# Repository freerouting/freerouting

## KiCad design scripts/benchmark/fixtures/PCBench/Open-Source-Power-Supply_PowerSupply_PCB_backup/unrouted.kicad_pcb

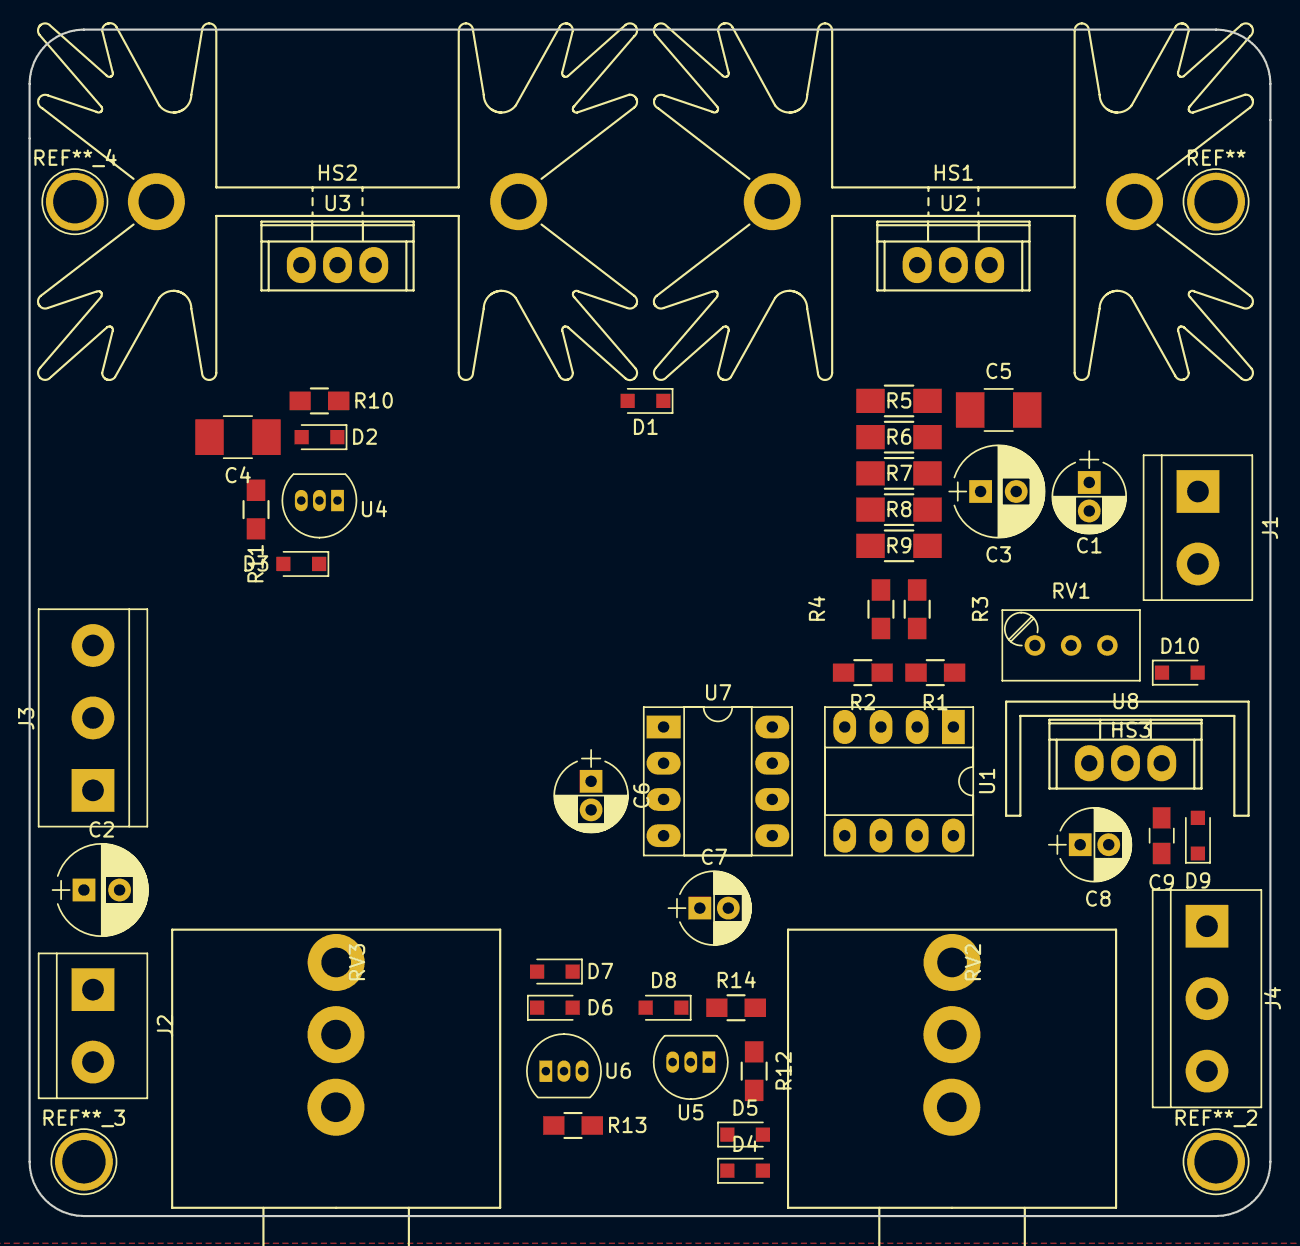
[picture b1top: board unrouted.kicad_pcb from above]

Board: 2 copper layers, 87.0 x 83.2 mm, 51 parts (0 on the bottom side), 23 nets, no tracks yet.

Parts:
C1, C6, C7, C8: 10u; CP_Radial_D5.0mm_P2.00mm
C2: 47uF electro; CP_Radial_D6.3mm_P2.50mm
C3: 47u; CP_Radial_D6.3mm_P2.50mm
C4: 4.7u; C_1210_HandSoldering
C5: 4.7u (optional); C_1210_HandSoldering
C9: 0.1u; C_0805_HandSoldering
D1, D2, D3, D9, D10: 1N5819; D_SOD-323_HandSoldering
D4, D5, D6, D7, D8: 1N4448; D_SOD-323_HandSoldering
HS1, HS2: Heatsink; Heatsink_Fischer_SK129-STS_42x25mm_2xDrill2.5mm
HS3: Heatsink; TO220-Small-16mmx8mm
J1: Input Voltage; bornier2
J2: Output Voltage; bornier2
J3: Voltage Meter; bornier3
J4: Current Meter; bornier3
R1, R2: 50k; R_0805_HandSoldering
R3, R4: 10k; R_0805_HandSoldering
R5, R6, R7, R8, R9: 10; R_1206_HandSoldering
R10: 1k; R_0805_HandSoldering
R11, R13: 15; R_0805_HandSoldering
R12: 33; R_0805_HandSoldering
R14: 330; R_0805_HandSoldering
RV1: 100 (multiturn); Potentiometer_Trimmer_Bourns_3296W
RV2, RV3: 10k; Potentiometer-3596S-10k-Pot
U1: LT1013; DIP-8_W7.62mm_Socket_LongPads
U2: LT1086; TO-220
U3: LM1117-ADJ; TO-220
U4, U5, U6: LM334Z; TO-92_Inline_Narrow_Oval
U7: ICL7660; DIP-8_W7.62mm_Socket_LongPads
U8: LM7812CT; TO-220

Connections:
+12V: C9.1, D9.2, D10.1, J3.1, J4.1, U7.8, U8.3
+16V: C1.1, C8.1, D1.1, D9.1, J1.1, U1.8, U2.3, U8.1
-12V: C7.2, D8.1, R11.2, R13.2, R14.2, U1.4, U4.3, U6.3, U7.5
CurrentMeter: J4.2, R1.1, U1.1
GND: C1.2, C2.2, C3.2, C4.2, C5.2, C7.1, C8.2, C9.2, D3.2, D7.2, D10.2, J1.2, J2.2, J3.3, J4.3, R2.2, U7.3, U8.2
unnamed: C3.1, R4.2, R5.1, R6.1, R7.1, R8.1, R9.1, RV1.1, U3.3
unnamed: C4.1, D2.2, R10.2, RV3.1, U3.1
unnamed: C5.1, RV2.2, U2.1
unnamed: C6.1, U7.2
unnamed: C6.2, U7.4
unnamed: D4.1, D5.2
unnamed: D4.2, RV1.2, RV1.3, RV2.3
unnamed: D5.1, RV2.1, U5.1
unnamed: D6.1, RV3.2, RV3.3, U6.1
unnamed: D6.2, D7.1
unnamed: D8.2, R12.2, U5.3
unnamed: R1.2, R4.1, U1.2
unnamed: R2.1, R3.1, U1.3
unnamed: R3.2, R5.2, R6.2, R7.2, R8.2, R9.2, U2.2
unnamed: R11.1, U4.2
unnamed: R12.1, R14.1, U5.2
unnamed: R13.1, U6.2
VoltageMeter: C2.1, D1.2, D2.1, D3.1, J2.1, J3.2, R10.1, U3.2, U4.1

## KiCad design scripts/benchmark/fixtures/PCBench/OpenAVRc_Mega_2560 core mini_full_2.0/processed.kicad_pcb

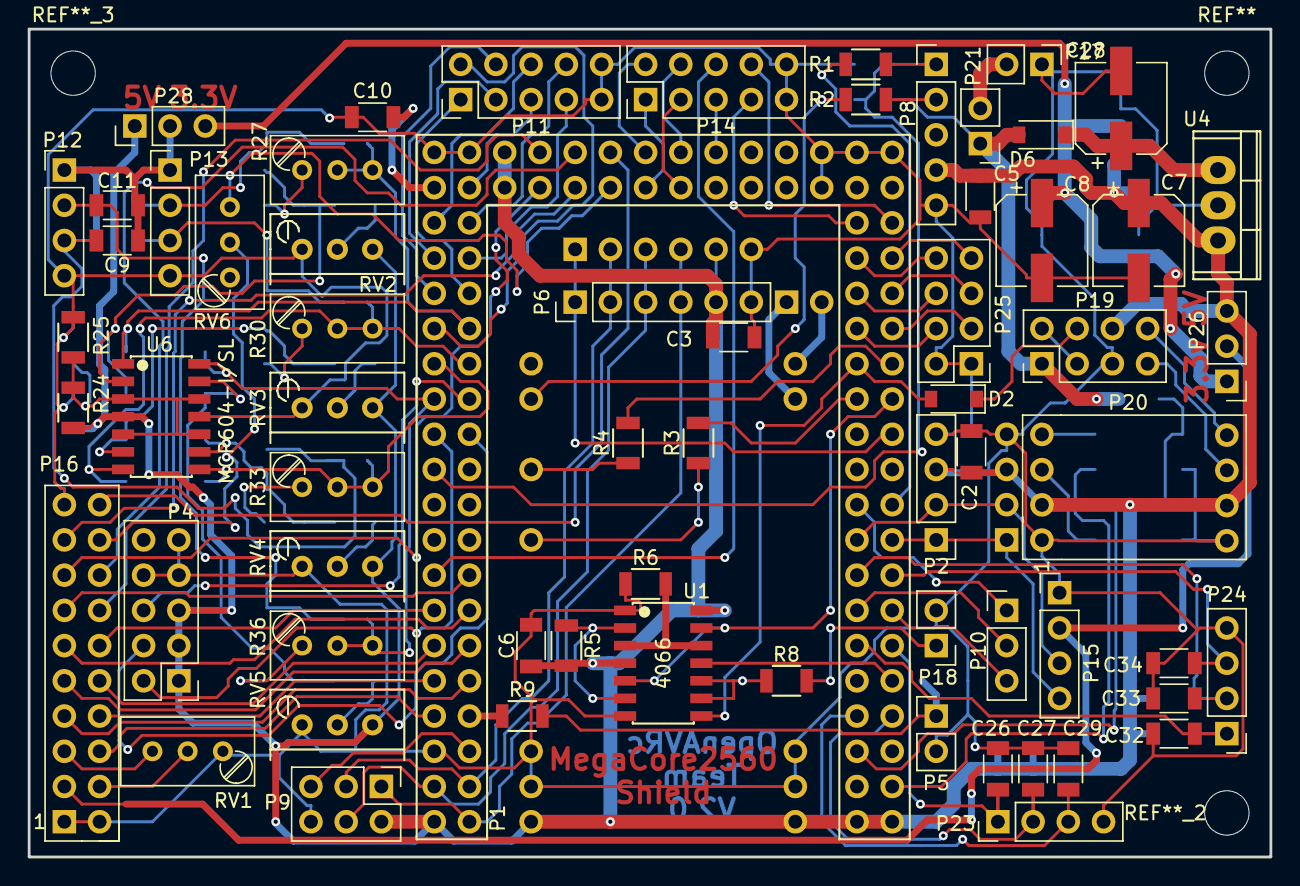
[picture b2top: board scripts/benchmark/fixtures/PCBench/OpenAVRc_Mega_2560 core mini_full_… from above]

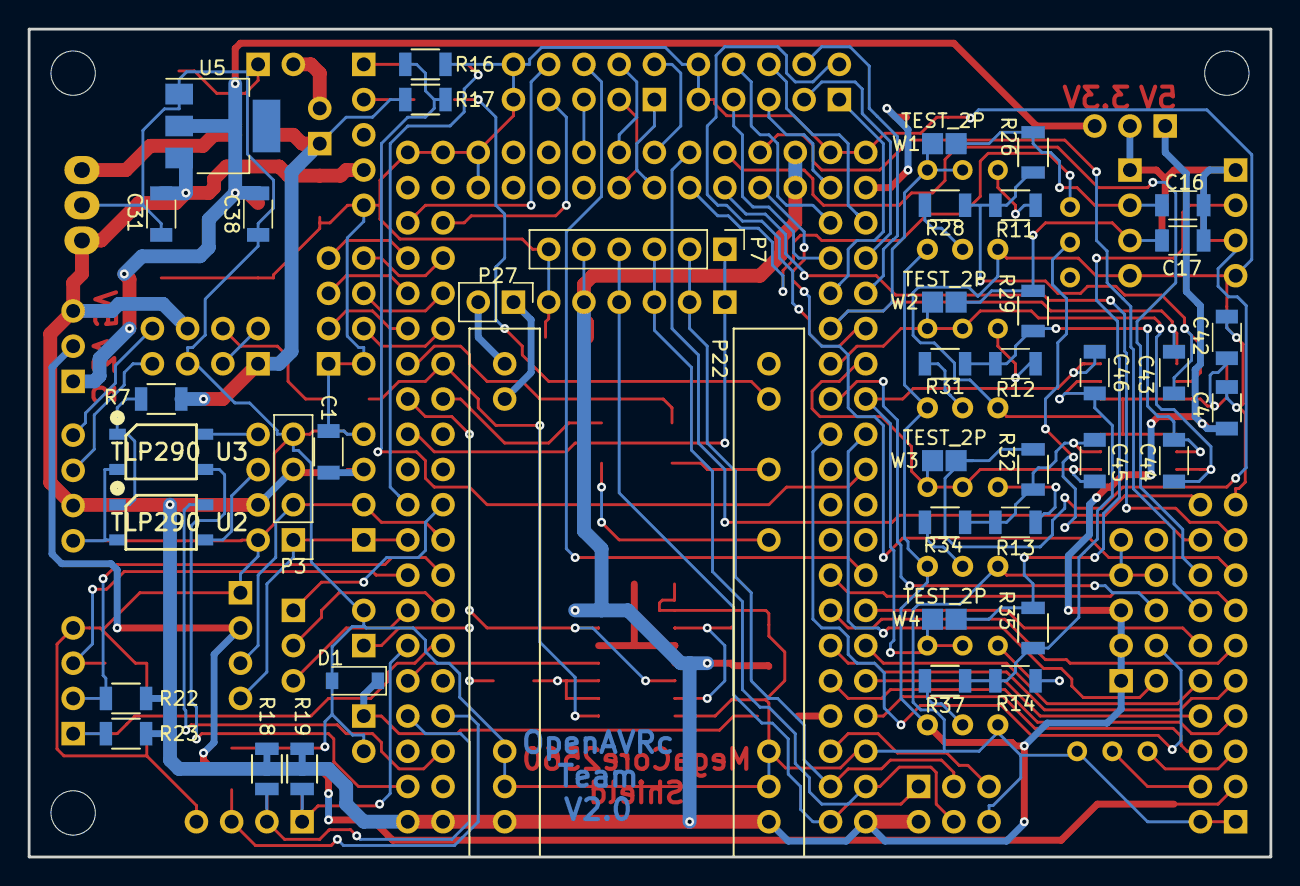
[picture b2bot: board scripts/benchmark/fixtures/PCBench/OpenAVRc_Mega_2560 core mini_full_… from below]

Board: 2 copper layers, 89.5 x 59.7 mm, 107 parts (42 on the bottom side), 117 nets.

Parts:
C1, C2, C3, C5: 47nF; C_1206
C4, C6, C9, C10, C11, C16, C17, C26, C27, C29, C31, C32, C33, C34, C38: 100nF; C_1206
C7, C8, C28: 47µF; CP_Elec_6.3x5.3
C42: 6.8nF; C_1206
C43, C44, C45, C46: 22nF; C_1206
D1, D2, D6: MBR0520; D_SOD-123
P1: 2560-core; Connectors-2560-core
P2: Clock; Pin_Header_Straight_1x04_Pitch2.54mm
P3: Option; Pin_Header_Straight_1x04_Pitch2.54mm
P4: Potentiometre; Pin_Header_Straight_2x05_Pitch2.54mm
P5: Vibreur; Pin_Header_Straight_1x02_Pitch2.54mm
P6: Micro_sd; Pin_Header_Straight_1x06_Pitch2.54mm
P7: Option; Pin_Header_Straight_1x06_Pitch2.54mm
P8: Audio; Pin_Header_Straight_1x05_Pitch2.54mm
P9: SPI; Pin_Header_Straight_2x03_Pitch2.54mm
P10: SPI_libre; Pin_Header_Straight_1x03_Pitch2.54mm
P11: Trim; Pin_Header_Straight_2x05_Pitch2.54mm
P12: Stick_left; Pin_Header_Straight_1x04_Pitch2.54mm
P13: Stick_right; Pin_Header_Straight_1x04_Pitch2.54mm
P14: Switch; Pin_Header_Straight_2x05_Pitch2.54mm
P15: LCD_I2C; Pin_Header_Straight_1x04_Pitch2.54mm
P16: LCD; Pin_Header_Straight_2x10_Pitch2.54mm
P17: Battery LIPO; Pin_Header_Straight_1x02_Pitch2.54mm
P18: Ecolage; Pin_Header_Straight_1x02_Pitch2.54mm
P19: Module_TX; Pin_Header_Straight_2x04_Pitch2.54mm
P20: Module_RS232/TTL; Con_RS232_TTL
P21: Sw_power; Pin_Header_Straight_1x02_Pitch2.54mm
P22: CONN_JQ6500_28P_mini; connector_mini-JQ6500-28P
P23: Rot_1; Pin_Header_Straight_1x04_Pitch2.54mm
P24: Rot_2; Pin_Header_Straight_1x04_Pitch2.54mm
P25: Key_select_menu_ESC; Pin_Header_Straight_2x04_Pitch2.54mm
P26: LCD_Vcc_select; Pin_Header_Straight_1x03_Pitch2.54mm
P27: HP; Pin_Header_Straight_1x02_Pitch2.54mm
P28: 5v/3,3v manches; Pin_Header_Straight_1x03_Pitch2.54mm
R1, R2: 22K; R_1206
R3: 18K; R_1206
R4: 1K; R_1206
R5, R6, R26, R28, R29, R31, R32, R34, R35, R37: 10K; R_1206
R7: 470; R_1206
R8: 200; R_1206
R9: 220; R_1206
R11, R12, R13, R14: 15K; R_1206
R16: 2.7K; R_1206
R17: 5.1K; R_1206
R18, R19, R22, R23: 5.1k; R_1206
R24, R25: 33K; R_1206
R27, R30, R33, R36: POT_22k; Potentiometer_Trimmer_Bourns_3296W
RV1: 220K; Potentiometer_Trimmer_Bourns_3296W
RV2, RV3, RV4, RV5: POT_100k; Potentiometer_Bourns_3296W_3-8Zoll_Inline_ScrewUp
RV6: 22K; Potentiometer_Trimmer_Bourns_3296W
U1: 4066; SOP14
U2, U3: TLP290; SOP4
U4: L4941; TO-220
U5: LD1117S33TR; SOT-223
U6: MCP604-I/SL; SOP14
W1, W2, W3, W4: TEST_2P; TESTPT

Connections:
+BATT: D6.2, P19.1, P21.1, R7.1, R17.2
/Isp_rst: P1.RESE, P9.5
/Key_DOWN: P1.49, P25.4
/Key_ESC: P1.44, P25.7
/Key_LEFT: P1.46, P25.5
/Key_MENU: P1.45, P25.8
/Key_RIGHT: P1.47, P25.6
/Key_UP: P1.48, P25.3
/LCD_VCC: P15.2, P16.3, P26.2
/Lcd_A0: P1.D32, P16.16
/Lcd_bla: P1.D35, RV6.3
/Lcd_cs: P1.D34, P16.20
/Lcd_db0: P1.D22, P16.6
/Lcd_db1: P1.D23, P16.7
/Lcd_db2: P1.D24, P16.8
/Lcd_db3: P1.D25, P16.9
/Lcd_db4: P1.D26, P16.10
/Lcd_db5: P1.D27, P16.11
/Lcd_db6: P1.D28, P16.12
/Lcd_db7: P1.D29, P16.13
/Lcd_e: P1.D30, P16.14
/Lcd_r/w: P1.D31, P16.15
/Lcd_rst: P1.D33, P16.17
/Lcd_vo: P16.4, RV1.2
/Microsd_CS: P1.53, P6.1, P7.1
/Miso: P1.MISO, P6.4, P7.4, P9.1
/Mosi: P1.MOSI, P6.3, P7.3, P9.4
/P3_3V: C8.1, C38.1, P26.1, P28.3, U5.2
/PH2: P1.PH2, P10.1
/PPM_TX_OUT: D2.1, P19.4
/PPM_in: P1.PE7, U1.11
/PPM_out: D2.2, P1.PW12, U1.8
/Pot_1: P1.A12, P4.6
/Pot_2: P1.A13, P4.2
/Pot_3: P1.A14, P4.4
/Power_manches: C9.1, C11.1, C16.1, C17.1, P12.1, P13.1, P28.2
/RXD2: P1.D17, P10.3
/RX_module: P19.8, P20.8
/Rot_1A: C29.1, P1.PWD2, P23.3
/Rot_1B: C27.1, P1.PWD3, P23.2, R18.2
/Rot_1push: C26.1, P1.D15, P23.1, R19.2
/Rot_2A: C34.1, P1.D19, P24.3
/Rot_2B: C33.1, P1.D18, P24.2, R22.2
/Rot_2push: C32.1, P1.D14, P24.1, R23.2
/Sck: P1.SCK, P6.2, P7.2, P9.3
/Scl: P1.D21, P2.1, P3.1, P15.4
/Sda: P1.D20, P2.2, P3.2, P15.3
/Sim_control: P1.PW11, U1.5, U1.13
/Stick_LH: C46.1, P1.A11, R36.2, R36.3, U6.14, W4.1
/Stick_LHcon: C9.2, P12.2, R35.2, W4.2
/Stick_LV: C45.1, P1.A9, R33.2, R33.3, U6.8, W3.1
/Stick_LVcon: C11.2, P12.3, R32.2, W3.2
/Stick_RH: C43.1, P1.A8, R27.2, R27.3, U6.1, W1.1
/Stick_RHcon: C16.2, P13.2, R26.2, W1.2
/Stick_RV: C44.1, P1.A10, R30.2, R30.3, U6.7, W2.1
/Stick_RVcon: C17.2, P13.3, R29.2, W2.2
/Sw_ailDR: P1.D38, P14.5
/Sw_eleDR: P1.43, P14.7
/Sw_gear: P1.D40, P14.4
/Sw_id1: P1.D37, P14.1
/Sw_id2: P1.D36, P14.2
/Sw_rudDR: P1.D41, P14.3
/Sw_thcut: P1.D39, P14.6
/Sw_turn: P1.42, P14.8
/TXD2: P1.D16, P10.2
/TX_module: P19.7, P20.7
/Tele_RX: P1.RXD, U3.3
/Tele_TX: P1.TXD, U2.4
/Trim_LH->: P1.A6, P11.1
/Trim_LH<-: P1.A7, P11.2
/Trim_LV->: P1.A4, P11.7
/Trim_LV<-: P1.A5, P11.4
/Trim_RH->: P1.A0, P11.5
/Trim_RH<-: P1.A1, P11.6
/Trim_RV->: P1.A2, P11.8
/Trim_RV<-: P1.A3, P11.3
/U_batt: P1.A15, R16.2, R17.1
/VREF: C10.1, P1.VREF
/Vibreur: P1.PJ7, R9.2
/audio_left_in: P1.PWD6, R1.2
/audio_right_in: P22.DACL, R2.2
/core_pw10: P1.PW10, R3.1
/core_pw13: P1.PW13, R4.1
GND: C1.1, C2.1, C3.1, C4.2, C5.1, C6.2, C7.2, C8.2, C10.2, C26.2, C27.2, C28.2, C29.2, C31.2, C32.2, C33.2, C34.2, C38.2, C42.2, D1.2, P1.GND, P2.4, P3.4, P4.7, P4.8, P4.9, P5.2, P6.6, P7.6, P8.5, P9.6, P11.9, P11.10, P12.4, P13.4, P14.9, P14.10, P15.1, P16.1, P16.2, P16.19, P17.1, P18.2, P19.5, P20.1, P20.5, P22.GND, P23.4, P24.4, P25.1, P25.2, R6.1, R16.1, R25.2, RV1.1, RV2.1, RV3.1, RV4.1, RV5.1, U1.1, U1.7, U2.2, U3.2, U4.2, U5.1, U6.11
unnamed: C28.1, D6.1, U4.1
unnamed: C42.1, R24.2, R25.1, U6.3, U6.5, U6.10, U6.12
unnamed: C43.2, R11.2, R26.1, R28.1, U6.2
unnamed: C44.2, R12.2, R29.1, R31.1, U6.6
unnamed: C45.2, R13.2, R32.1, R34.1, U6.9
unnamed: C46.2, R14.2, R35.1, R37.1, U6.13
unnamed: D1.1, P5.1, R9.1
unnamed: P8.1, R1.1
unnamed: P8.2, R2.1
unnamed: P16.5, RV1.3
unnamed: P16.18, RV6.2
unnamed: P17.2, P21.2
unnamed: P18.1, R8.1
unnamed: P19.2, P19.3
unnamed: P20.3, U2.3
unnamed: P20.4, U3.4
unnamed: P22.BUSY, R3.2
unnamed: P22.RX, R4.2
unnamed: P22.SPK+, P27.2
unnamed: P22.SPK-, P27.1
unnamed: R5.2, U1.2, U1.6
unnamed: R6.2, U1.3, U1.12
unnamed: R7.2, U2.1, U3.1
unnamed: R8.2, U1.9, U1.10
unnamed: R11.1, R27.1
unnamed: R12.1, R30.1
unnamed: R13.1, R33.1
unnamed: R14.1, R36.1
unnamed: R28.2, RV2.2
unnamed: R31.2, RV3.2
unnamed: R34.2, RV4.2
unnamed: R37.2, RV5.2
VCC: C1.2, C2.2, C3.2, C4.1, C5.2, C6.1, C7.1, C31.1, P1.VCC, P2.3, P3.3, P4.1, P4.3, P4.5, P6.5, P7.5, P8.4, P9.2, P19.6, P20.2, P20.6, P22.VCC, P26.3, P28.1, R5.1, R18.1, R19.1, R22.1, R23.1, R24.1, RV2.3, RV3.3, RV4.3, RV5.3, U1.4, U1.14, U4.3, U5.3, U6.4

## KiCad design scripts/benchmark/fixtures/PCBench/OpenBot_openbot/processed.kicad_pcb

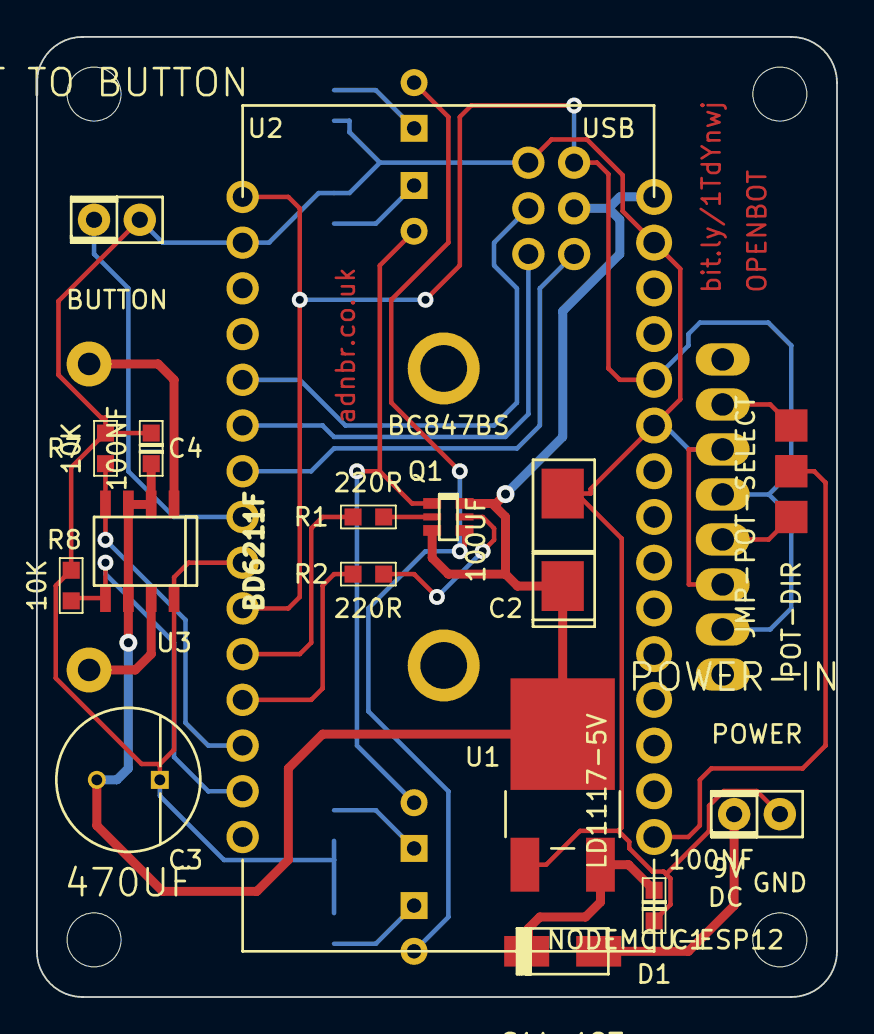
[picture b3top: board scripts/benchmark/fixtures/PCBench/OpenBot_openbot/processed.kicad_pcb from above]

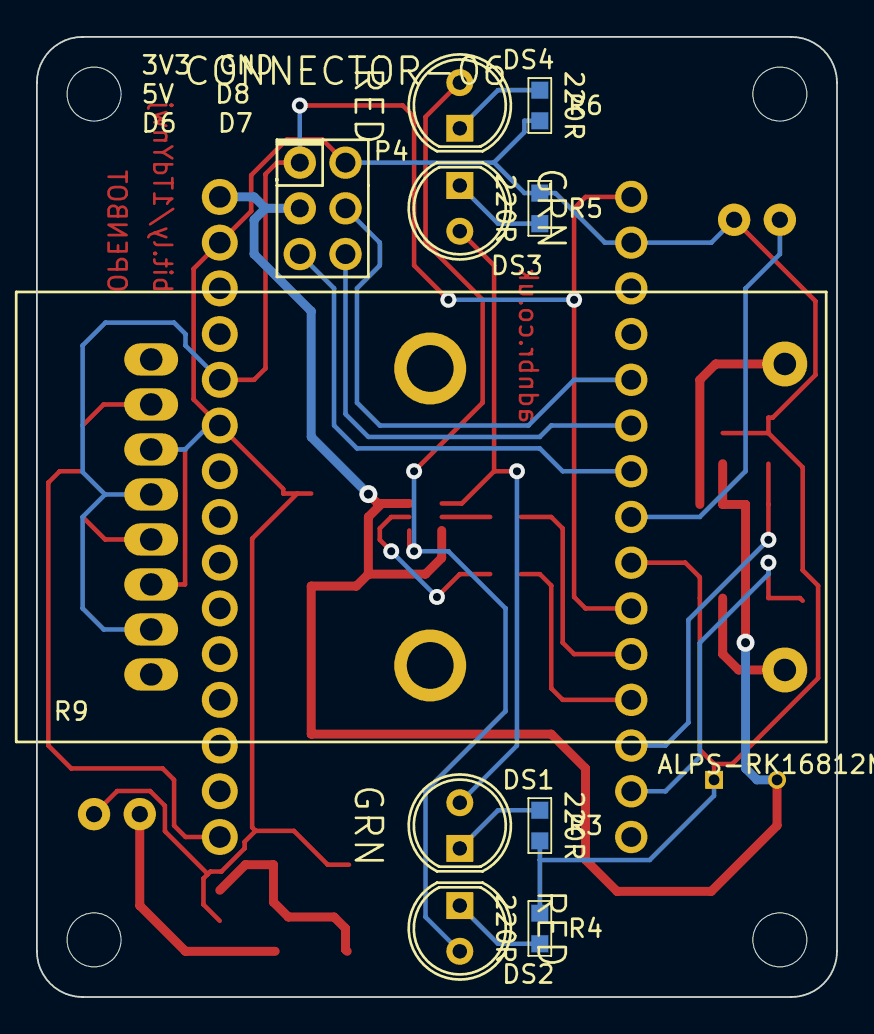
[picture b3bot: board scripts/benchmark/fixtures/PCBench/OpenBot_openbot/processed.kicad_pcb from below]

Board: 2 copper layers, 44.4 x 53.3 mm, 30 parts (10 on the bottom side), 26 nets.

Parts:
BUTTON: JST TO BUTTON; CONN-02
C1, C4: 100NF; CAPACITOR-NP-0603-REFLOW
C2: 100UF; CAP_POL_KEMET_C
C3: 470UF; CAPACITOR-POL-D_8MMxP_3.5MM
D1: S1A-127; DIODE-SMA
DS1, DS3: GRN; LED-5MM
DS2, DS4: RED; LED-5MM
M3-HOLE, M3-HOLE_2, M3-HOLE_3, M3-HOLE_4: VAL**; M3-HOLE
P4: CONNECTOR-06; CONN-06-2x3
POT-DIR: JMP-POT-SELECT; SJ-03
POWER: POWER-IN; CONN-02
Q1: BC847BS; SOT363
R1, R2, R3, R4, R5, R6: 220R; RESISTOR-0603-REFLOW
R7, R8: 10K; RESISTOR-0603-REFLOW
R9: ALPS-RK16812MG; ALPS-RK16812MG-10kBx2
U1: LD1117-5V; TO-252
U2: NODEMCU-ESP12; NODEMCU-DEVKIT
U3: BD6211F; SOP-8

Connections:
3V3: P4.1, R9.A1, R9.B3, U2.11, U2.16, U2.25
+5V: C2.A, C3.A, C4.2, P4.2, Q1.3, Q1.6, U1.2, U2.15, U3.2, U3.3, U3.6
/MOTOR-A: R9.MB, U3.1
/MOTOR-B: R9.MA, U3.7
GND: BUTTON.2, C1.1, C2.C, C3.C, C4.1, P4.6, POWER.2, R3.1, R4.1, R5.1, R6.1, R7.1, R8.1, R9.A3, R9.B1, U1.1, U2.10, U2.14, U2.17, U2.24, U3.8
LED-GREEN: R1.2, U2.26
LED-RED: R2.2, U2.27
MOTOR-FWD: R7.2, U2.28, U3.4
MOTOR-REV: R8.2, U2.29, U3.5
unnamed: POT-DIR.2, U2.1
unnamed: POT-DIR.3, R9.B2
unnamed: POT-DIR.1, R9.A2
unnamed: D1.A, POWER.1
unnamed: P4.3, U2.22
unnamed: P4.4, U2.21
unnamed: Q1.5, R2.1
unnamed: Q1.2, R1.1
unnamed: C1.2, D1.C, U1.3
unnamed: P4.5, U2.20
unnamed: DS2.C, R4.2
unnamed: DS4.C, R6.2
unnamed: DS1.A, DS3.A, Q1.1
unnamed: BUTTON.1, U2.23
unnamed: DS1.C, R3.2
unnamed: DS3.C, R5.2
unnamed: DS2.A, DS4.A, Q1.4

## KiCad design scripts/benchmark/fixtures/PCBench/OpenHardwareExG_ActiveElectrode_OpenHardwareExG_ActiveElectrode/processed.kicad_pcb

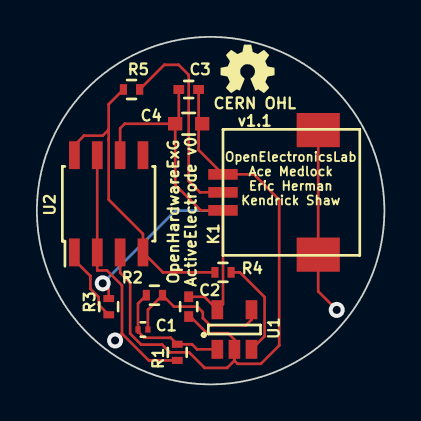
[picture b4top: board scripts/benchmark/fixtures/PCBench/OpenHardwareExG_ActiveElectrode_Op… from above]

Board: 4 copper layers, 19.3 x 19.3 mm, 13 parts (1 on the bottom side), 10 nets.

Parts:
C1: 1nF; C_0201
C2, C3: 1uF; C_0402
C4: 10uF; C_0603
K1: CONN_3; DF50A-3P-1H
P1: CONN_1; electrode_pad
R1, R3, R5: 100; R_0402
R2, R4: 10k; R_0402
U1: LMP7715; SOT-23-5
U2: LMP7721; SOIC-8_3.9x4.9mm_Pitch1.27mm

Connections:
+5V: C2.1, C3.1, C4.1, K1.1, U1.5, U2.6
/BUFFERED_INPUT: R4.2, R5.1, U2.4, U2.8
/ELECTRODE: P1.1, R3.1
/GUARD_RING: R1.2, U2.2, U2.7
/GUARD_RING_DRIVER: C1.1, R1.1, R2.1, U1.1
/GUARD_RING_FILTERED_FEEDBACK: C1.2, R2.2, U1.4
/GUARD_RING_INPUT: R4.1, U1.3
/LINE_OUT: K1.2, R5.2
/PROTECTED_ELECTRODE: R3.2, U2.1
GND: C2.2, C3.2, C4.2, K1.3, U1.2, U2.3

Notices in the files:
scripts/benchmark/fixtures/PCBench/OpenHardwareExG_ActiveElectrode_OpenHardwareExG_ActiveElectrode/processed.kicad_pcb:
CERN OHL
